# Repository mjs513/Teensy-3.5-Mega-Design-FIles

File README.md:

# Teensy-3.5-Mega-Design-FIles
Kicad/Gerber files for the Teensy 3.5 Breakout Board

See this thread for illustration of board, https://forum.pjrc.com/threads/36244-Teensy-3-5-3-6-Breakout-board-to-test-things-with/page4

Files are provide as is, no guarantee that all connections are 100% correct.  This is a work in progress.  Use at your own risk and check for errors.  

The design was made in KiCad with an export of the Gerber files.

If you find any errors please let me know.  Just to let you know i am currently using this board in my projects.

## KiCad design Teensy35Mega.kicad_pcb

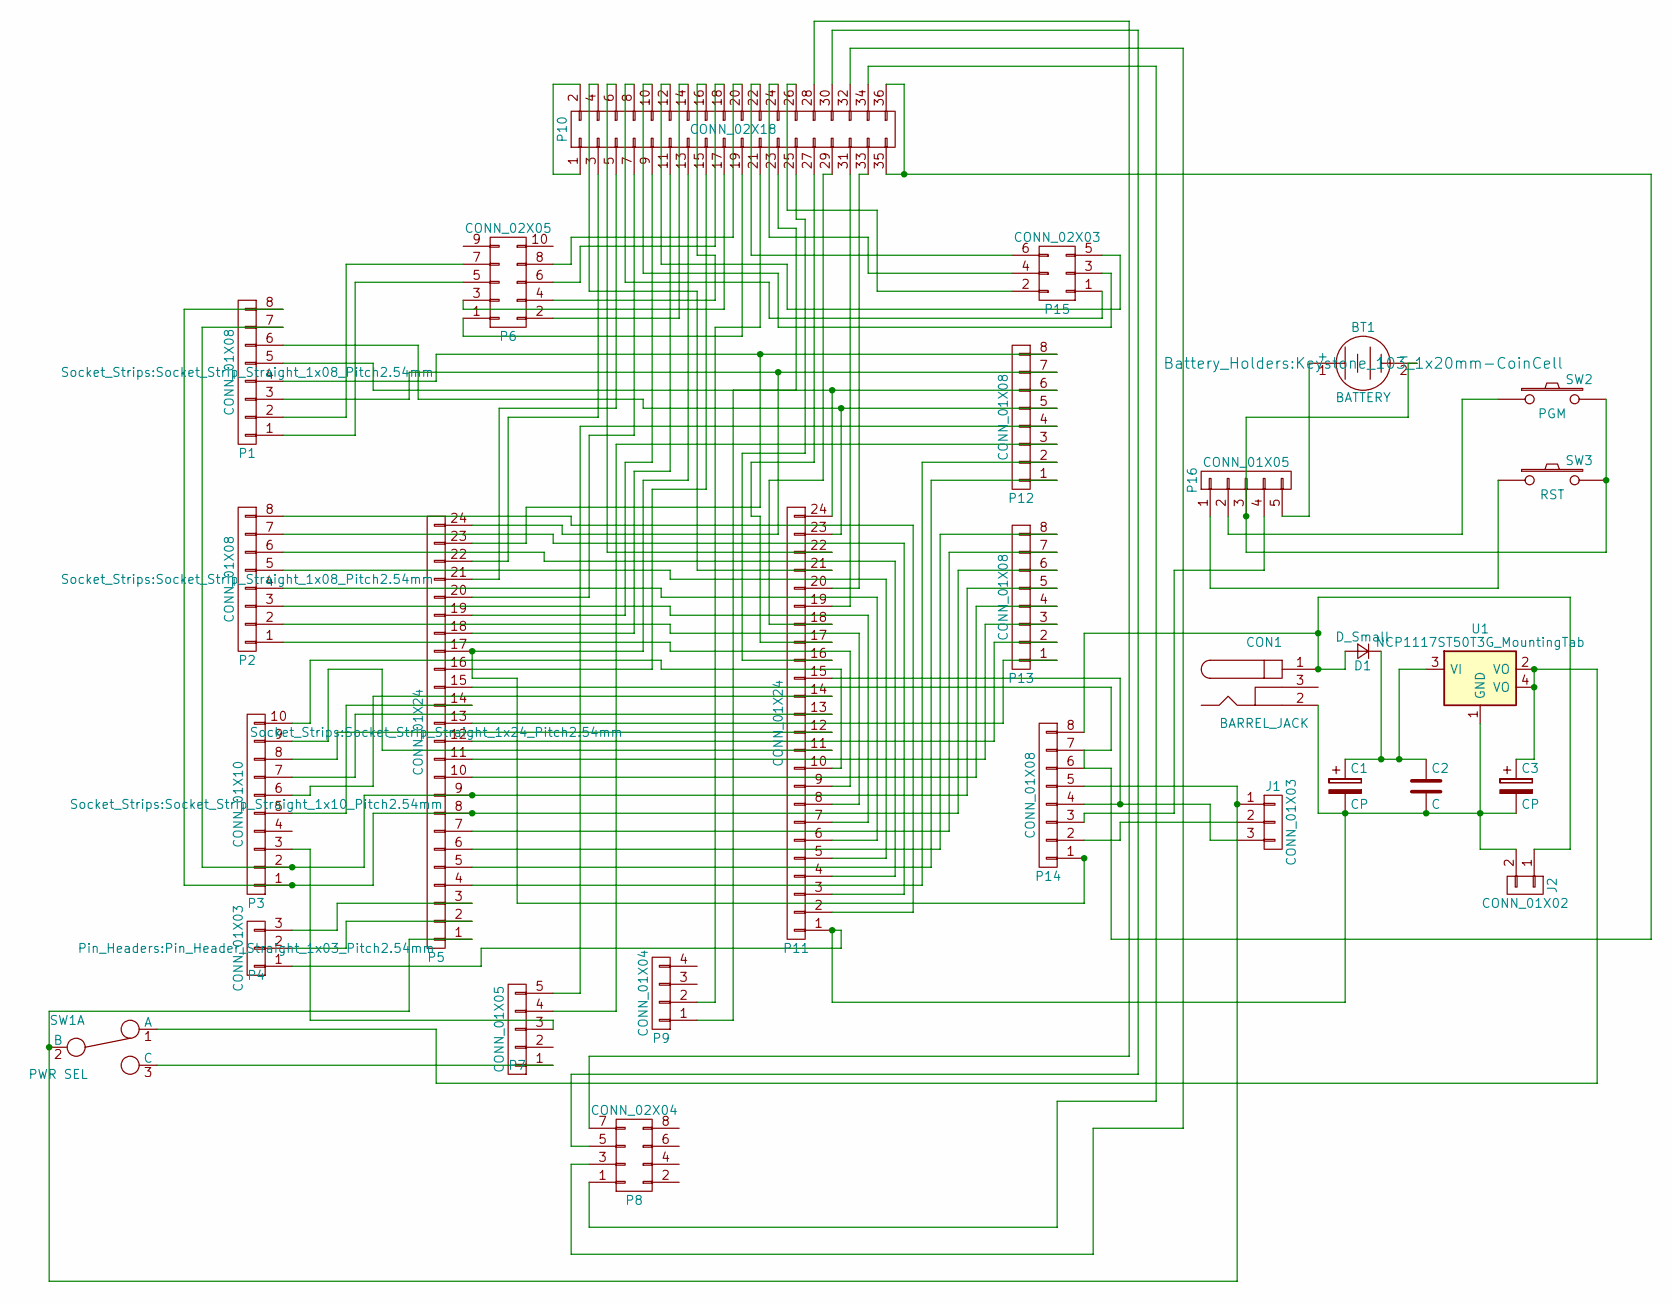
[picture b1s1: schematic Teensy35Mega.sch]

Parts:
BT1: BATTERY; Keystone_103_1x20mm-CoinCell
C1, C3: CP; CP_Radial_D6.3mm_P2.50mm
C2: C; C_Disc_D3.0mm_W2.0mm_P2.50mm
CON1: BARREL_JACK
D1: D_Small; D_DO-15_P10.16mm_Horizontal
J1: CONN_01X03; Pin_Header_Straight_1x03_Pitch2.54mm
J2: CONN_01X02; Pin_Header_Straight_1x02_Pitch2.54mm
P1, P2, P12, P13, P14: CONN_01X08; Socket_Strip_Straight_1x08_Pitch2.54mm
P3: CONN_01X10; Socket_Strip_Straight_1x10_Pitch2.54mm
P4: CONN_01X03; Pin_Header_Straight_1x03_Pitch2.54mm
P5, P11: CONN_01X24; Socket_Strip_Straight_1x24_Pitch2.54mm
P6: CONN_02X05; Socket_Strip_Straight_2x05_Pitch2.54mm
P7, P16: CONN_01X05; Socket_Strip_Straight_1x05_Pitch2.54mm
P8: CONN_02X04; Socket_Strip_Straight_2x04_Pitch2.54mm
P9: CONN_01X04; Socket_Strip_Straight_1x04_Pitch2.54mm
P10: CONN_02X18; Socket_Strip_Straight_2x18_Pitch2.54mm
P15: CONN_02X03; Socket_Strip_Straight_2x03_Pitch2.54mm
SW1: PWR SEL; SW_SPDT
SW2: PGM; SW_PUSH
SW3: RST; SW_PUSH
U1: NCP1117ST50T3G_MountingTab; SOT-223

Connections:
unnamed: BT1.1 (+), P16.5
unnamed: BT1.2 (-), P16.3, SW2.2, SW3.2
unnamed: C1.1, C2.1, D1.1 (K), U1.3 (VI)
unnamed: C1.2, C2.2, C3.2, CON1.2, J2.2, P4.1, P11.1, U1.1 (GND)
unnamed: C3.1, SW1.1 (A), U1.2 (VO), U1.4 (VO)
unnamed: CON1.1, D1.2 (A), J2.1, P14.8
unnamed: J1.1, P5.1, P14.5, SW1.2 (B)
unnamed: J1.2, P14.2
unnamed: J1.3, P11.15, P14.4
unnamed: P1.1, P6.5
unnamed: P1.2, P6.7
unnamed: P1.3, P5.24, P12.7
unnamed: P1.4, P5.23, P12.8
unnamed: P1.5, P11.24, P12.6
unnamed: P1.6, P11.23, P12.5
unnamed: P1.7, P3.2, P5.9, P13.5
unnamed: P1.8, P3.1, P5.8, P13.6
unnamed: P3.3, P7.3
unnamed: P3.5, P5.14
unnamed: P4.2, P5.2
unnamed: P4.3, P5.3
unnamed: P7.1, SW1.3 (C)
unnamed: P10.1, P10.2
unnamed: P5.22, P10.3
unnamed: P10.4, P11.21
unnamed: P5.21, P10.5
unnamed: P10.6, P11.22
unnamed: P5.20, P10.7
unnamed: P10.8, P15.1
unnamed: P5.19, P10.9
unnamed: P10.10, P15.3
unnamed: P5.18, P10.11
unnamed: P10.12, P15.5
unnamed: P5.17, P10.13, P14.1
unnamed: P6.2, P10.14
unnamed: P5.16, P10.15
unnamed: P6.4, P10.16
unnamed: P6.3, P10.17
unnamed: P6.6, P10.18
unnamed: P6.1, P10.19
unnamed: P6.8, P10.20
unnamed: P9.2, P10.21
unnamed: P10.22, P15.6
unnamed: P9.1, P10.23
unnamed: P10.24, P15.4
unnamed: P10.25, P11.16
unnamed: P10.26, P15.2
unnamed: P10.27, P11.17
unnamed: P8.7, P10.28
unnamed: P10.29, P11.18
unnamed: P8.5, P10.30
unnamed: P10.31, P11.19
unnamed: P8.3, P10.32
unnamed: P10.33, P11.20
unnamed: P8.1, P10.34
unnamed: P5.15, P10.35, P10.36, P14.6, P14.7
unnamed: P2.8, P11.2
unnamed: P2.7, P11.3
unnamed: P2.6, P11.4
unnamed: P2.5, P11.5
unnamed: P2.4, P11.6
unnamed: P2.3, P11.7
unnamed: P2.2, P11.8
unnamed: P2.1, P11.9
unnamed: P3.10, P11.10
unnamed: P3.9, P11.11
unnamed: P3.8, P11.12
unnamed: P3.7, P11.13
unnamed: P3.6, P11.14
unnamed: P5.5, P12.1
unnamed: P5.4, P12.2
unnamed: P7.4, P12.3
unnamed: P7.5, P12.4
unnamed: P5.13, P13.1
unnamed: P5.12, P13.2
unnamed: P5.11, P13.3
unnamed: P5.10, P13.4
unnamed: P5.7, P13.7
unnamed: P5.6, P13.8
unnamed: P14.3, P16.4
unnamed: P16.1, SW3.1
unnamed: P16.2, SW2.1

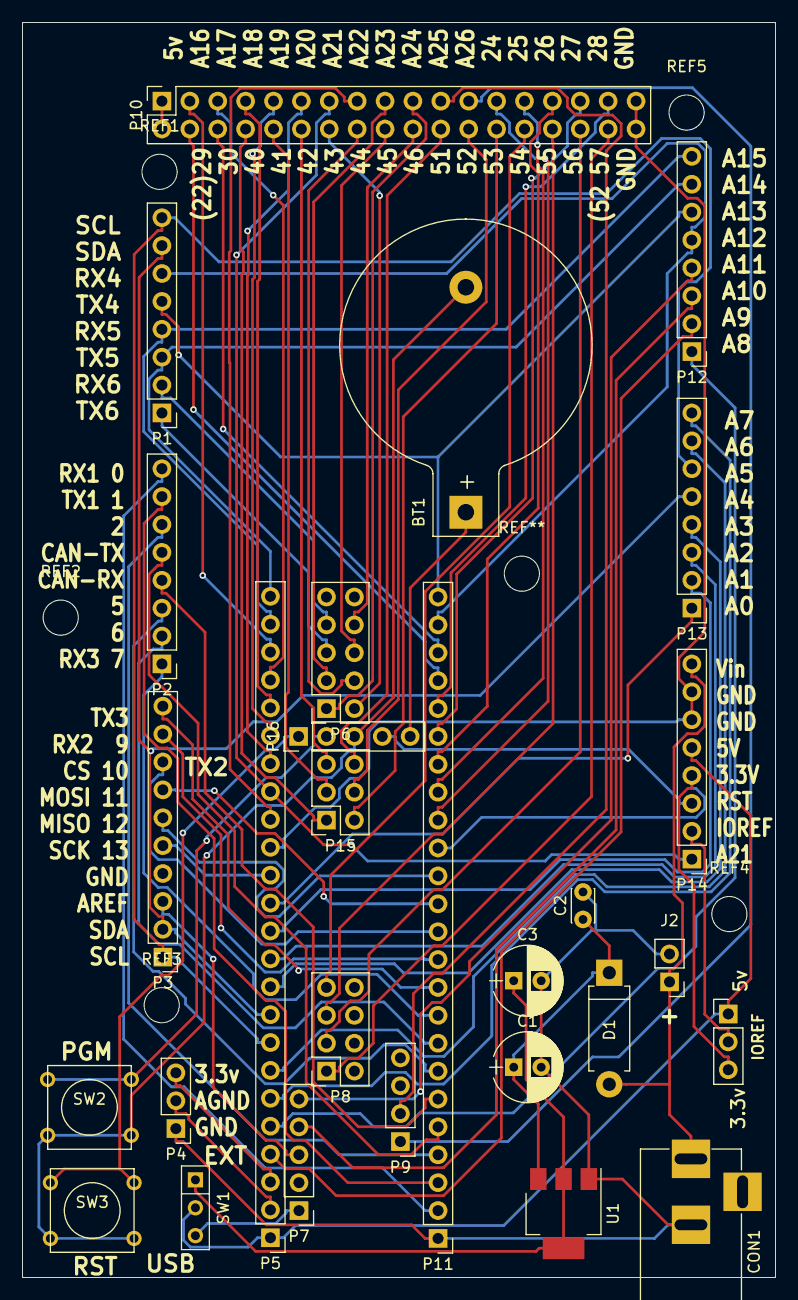
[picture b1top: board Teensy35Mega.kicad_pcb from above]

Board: 2 copper layers, 68.6 x 114.3 mm, 33 parts (0 on the bottom side), 82 nets.

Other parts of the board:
REF1, REF2, REF3, REF4, REF5: MountingHole_3.2mm_M3_ISO14580_Pad; MountingHole_3.2mm_M3

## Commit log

2018-06-27 Initial add of files and partial BOM
2018-06-28 Updated P8 connections & Layout
    Updated P8 connections. per @boelle on PRJC Forum
2018-08-29 Updated BOM
